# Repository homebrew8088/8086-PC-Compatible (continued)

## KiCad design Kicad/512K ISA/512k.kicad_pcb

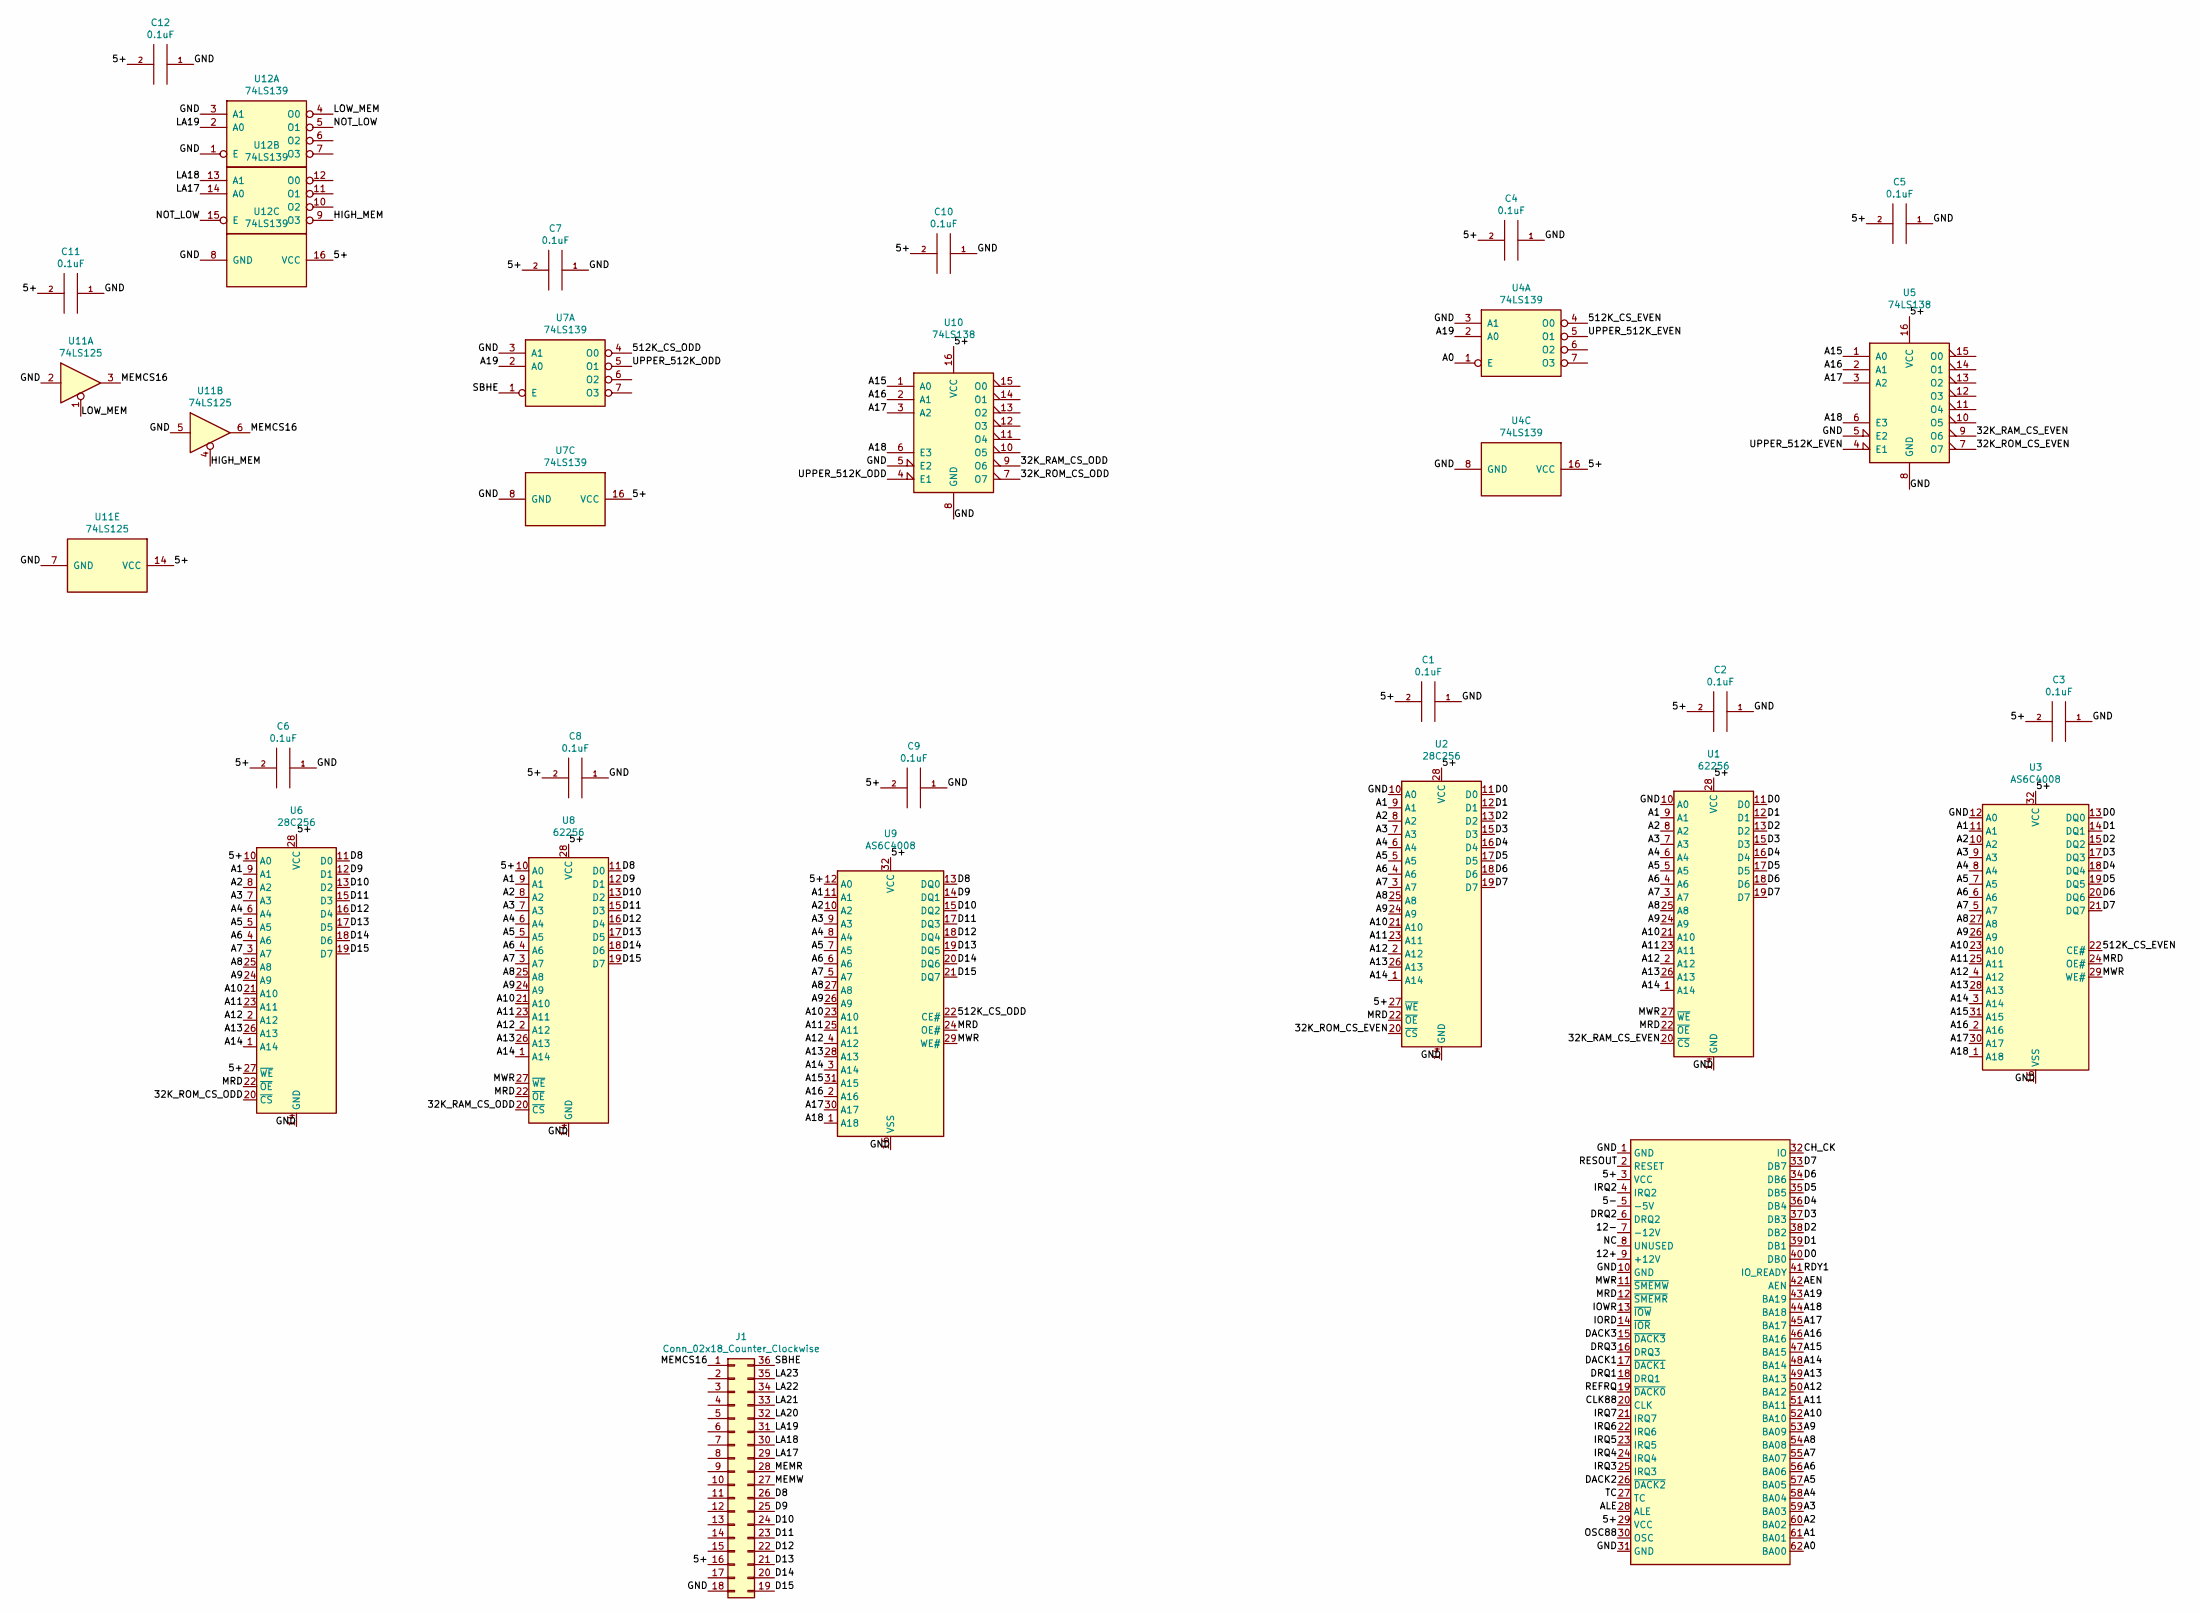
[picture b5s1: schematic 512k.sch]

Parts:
C1, C2, C3, C4, C5, C6, C7, C8, C9, C10, C11, C12: 0.1uF; C_Disc_D4.3mm_W1.9mm_P5.00mm
J1: Conn_02x18_Counter_Clockwise; 36_EDGE_CARD_BUS
J9: Bus_ISA_8bit; BUS_8_BIT
U1, U8: 62256; DIP-28_W15.24mm
U2, U6: 28C256; DIP_Socket-28_W11.9_W12.7_W15.24_W17.78_W18.5_3M_228-1277-0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
U3, U9: AS6C4008; DIP-32_W15.24mm
U4, U7, U12: 74LS139; DIP-16_W7.62mm
U5, U10: 74LS138; DIP-16_W7.62mm
U11: 74LS125; DIP-14_W7.62mm

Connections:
/5+: C1.2, C2.2, C3.2, C4.2, C5.2, C6.2, C7.2, C8.2, C9.2, C10.2, C11.2, C12.2, J1.16, J9.3 (VCC), J9.29 (VCC), U1.28 (VCC), U2.27 (~WE), U2.28 (VCC), U3.32 (VCC), U4.16 (VCC), U5.16 (VCC), U6.10 (A0), U6.27 (~WE), U6.28 (VCC), U7.16 (VCC), U8.10 (A0), U8.28 (VCC), U9.12 (A0), U9.32 (VCC), U10.16 (VCC), U11.14 (VCC), U12.16 (VCC)
/5-: J9.5 (-5V)
/12+: J9.9 (+12V)
/12-: J9.7 (-12V)
/32K_RAM_CS_EVEN: U1.20 (~CS), U5.9 (O6)
/32K_RAM_CS_ODD: U8.20 (~CS), U10.9 (O6)
/32K_ROM_CS_EVEN: U2.20 (~CS), U5.7 (O7)
/32K_ROM_CS_ODD: U6.20 (~CS), U10.7 (O7)
/512K_CS_EVEN: U3.22 (CE#), U4.4 (O0)
/512K_CS_ODD: U7.4 (O0), U9.22 (CE#)
/A0: J9.62 (BA00), U4.1 (E)
/A1: J9.61 (BA01), U1.9 (A1), U2.9 (A1), U3.11 (A1), U6.9 (A1), U8.9 (A1), U9.11 (A1)
/A2: J9.60 (BA02), U1.8 (A2), U2.8 (A2), U3.10 (A2), U6.8 (A2), U8.8 (A2), U9.10 (A2)
/A3: J9.59 (BA03), U1.7 (A3), U2.7 (A3), U3.9 (A3), U6.7 (A3), U8.7 (A3), U9.9 (A3)
/A4: J9.58 (BA04), U1.6 (A4), U2.6 (A4), U3.8 (A4), U6.6 (A4), U8.6 (A4), U9.8 (A4)
/A5: J9.57 (BA05), U1.5 (A5), U2.5 (A5), U3.7 (A5), U6.5 (A5), U8.5 (A5), U9.7 (A5)
/A6: J9.56 (BA06), U1.4 (A6), U2.4 (A6), U3.6 (A6), U6.4 (A6), U8.4 (A6), U9.6 (A6)
/A7: J9.55 (BA07), U1.3 (A7), U2.3 (A7), U3.5 (A7), U6.3 (A7), U8.3 (A7), U9.5 (A7)
/A8: J9.54 (BA08), U1.25 (A8), U2.25 (A8), U3.27 (A8), U6.25 (A8), U8.25 (A8), U9.27 (A8)
/A9: J9.53 (BA09), U1.24 (A9), U2.24 (A9), U3.26 (A9), U6.24 (A9), U8.24 (A9), U9.26 (A9)
/A10: J9.52 (BA10), U1.21 (A10), U2.21 (A10), U3.23 (A10), U6.21 (A10), U8.21 (A10), U9.23 (A10)
/A11: J9.51 (BA11), U1.23 (A11), U2.23 (A11), U3.25 (A11), U6.23 (A11), U8.23 (A11), U9.25 (A11)
/A12: J9.50 (BA12), U1.2 (A12), U2.2 (A12), U3.4 (A12), U6.2 (A12), U8.2 (A12), U9.4 (A12)
/A13: J9.49 (BA13), U1.26 (A13), U2.26 (A13), U3.28 (A13), U6.26 (A13), U8.26 (A13), U9.28 (A13)
/A14: J9.48 (BA14), U1.1 (A14), U2.1 (A14), U3.3 (A14), U6.1 (A14), U8.1 (A14), U9.3 (A14)
/A15: J9.47 (BA15), U3.31 (A15), U5.1 (A0), U9.31 (A15), U10.1 (A0)
/A16: J9.46 (BA16), U3.2 (A16), U5.2 (A1), U9.2 (A16), U10.2 (A1)
/A17: J9.45 (BA17), U3.30 (A17), U5.3 (A2), U9.30 (A17), U10.3 (A2)
/A18: J9.44 (BA18), U3.1 (A18), U5.6 (E3), U9.1 (A18), U10.6 (E3)
/A19: J9.43 (BA19), U4.2 (A0), U7.2 (A0)
/AEN: J9.42 (AEN)
/ALE: J9.28 (ALE)
/CH_CK: J9.32 (IO)
/CLK88: J9.20 (CLK)
/D0: J9.40 (DB0), U1.11 (D0), U2.11 (D0), U3.13 (DQ0)
/D1: J9.39 (DB1), U1.12 (D1), U2.12 (D1), U3.14 (DQ1)
/D2: J9.38 (DB2), U1.13 (D2), U2.13 (D2), U3.15 (DQ2)
/D3: J9.37 (DB3), U1.15 (D3), U2.15 (D3), U3.17 (DQ3)
/D4: J9.36 (DB4), U1.16 (D4), U2.16 (D4), U3.18 (DQ4)
/D5: J9.35 (DB5), U1.17 (D5), U2.17 (D5), U3.19 (DQ5)
/D6: J9.34 (DB6), U1.18 (D6), U2.18 (D6), U3.20 (DQ6)
/D7: J9.33 (DB7), U1.19 (D7), U2.19 (D7), U3.21 (DQ7)
/D8: J1.26, U6.11 (D0), U8.11 (D0), U9.13 (DQ0)
/D9: J1.25, U6.12 (D1), U8.12 (D1), U9.14 (DQ1)
/D10: J1.24, U6.13 (D2), U8.13 (D2), U9.15 (DQ2)
/D11: J1.23, U6.15 (D3), U8.15 (D3), U9.17 (DQ3)
/D12: J1.22, U6.16 (D4), U8.16 (D4), U9.18 (DQ4)
/D13: J1.21, U6.17 (D5), U8.17 (D5), U9.19 (DQ5)
/D14: J1.20, U6.18 (D6), U8.18 (D6), U9.20 (DQ6)
/D15: J1.19, U6.19 (D7), U8.19 (D7), U9.21 (DQ7)
/DACK1: J9.17 (~DACK1)
/DACK2: J9.26 (~DACK2)
/DACK3: J9.15 (~DACK3)
/DRQ1: J9.18 (DRQ1)
/DRQ2: J9.6 (DRQ2)
/DRQ3: J9.16 (DRQ3)
/GND: C1.1, C2.1, C3.1, C4.1, C5.1, C6.1, C7.1, C8.1, C9.1, C10.1, C11.1, C12.1, J1.18, J9.1 (GND), J9.10 (GND), J9.31 (GND), U1.10 (A0), U1.14 (GND), U2.10 (A0), U2.14 (GND), U3.12 (A0), U3.16 (VSS), U4.3 (A1), U4.8 (GND), U5.5 (E2), U5.8 (GND), U6.14 (GND), U7.3 (A1), U7.8 (GND), U8.14 (GND), U9.16 (VSS), U10.5 (E2), U10.8 (GND), U11.2, U11.5, U11.7 (GND), U12.1 (E), U12.3 (A1), U12.8 (GND); also elsewhere on the board
/HIGH_MEM: U11.4, U12.9 (O3)
/IORD: J9.14 (~IOR)
/IOWR: J9.13 (~IOW)
/IRQ2: J9.4 (IRQ2)
/IRQ3: J9.25 (IRQ3)
/IRQ4: J9.24 (IRQ4)
/IRQ5: J9.23 (IRQ5)
/IRQ6: J9.22 (IRQ6)
/IRQ7: J9.21 (IRQ7)
/LA17: J1.29, U12.14 (A0)
/LA18: J1.30, U12.13 (A1)
/LA19: J1.31, U12.2 (A0)
/LA20: J1.32
/LA21: J1.33
/LA22: J1.34
/LA23: J1.35
/LOW_MEM: U11.1, U12.4 (O0)
/MEMCS16: J1.1, U11.3, U11.6
/MEMR: J1.28
/MEMW: J1.27
/MRD: J9.12 (~SMEMR), U1.22 (~OE), U2.22 (~OE), U3.24 (OE#), U6.22 (~OE), U8.22 (~OE), U9.24 (OE#)
/MWR: J9.11 (~SMEMW), U1.27 (~WE), U3.29 (WE#), U8.27 (~WE), U9.29 (WE#)
/NC: J9.8 (UNUSED)
/NOT_LOW: U12.5 (O1), U12.15 (E)
/OSC88: J9.30 (OSC)
/RDY1: J9.41 (IO_READY)
/REFRQ: J9.19 (~DACK0)
/RESOUT: J9.2 (RESET)
/SBHE: J1.36, U7.1 (E)
/TC: J9.27 (TC)
/UPPER_512K_EVEN: U4.5 (O1), U5.4 (E1)
/UPPER_512K_ODD: U7.5 (O1), U10.4 (E1)

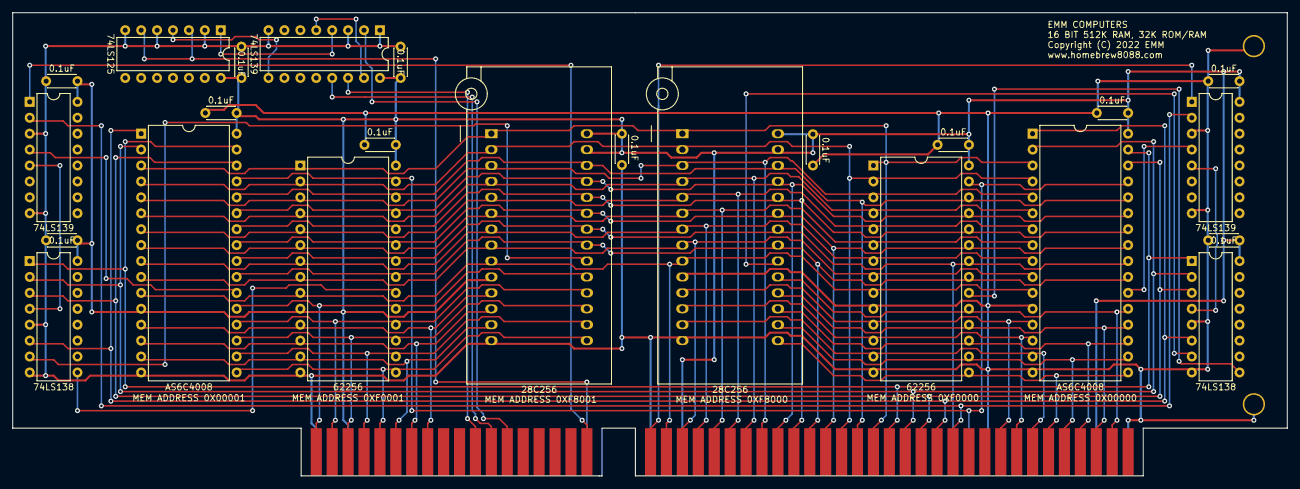
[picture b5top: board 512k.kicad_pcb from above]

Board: 2 copper layers, 203.4 x 73.9 mm, 28 parts (0 on the bottom side), 56 nets.

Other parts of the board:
R: L; Large_Via
R#2: L; Large_Via

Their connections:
/GND: R.1, R#2.1; also elsewhere on the board

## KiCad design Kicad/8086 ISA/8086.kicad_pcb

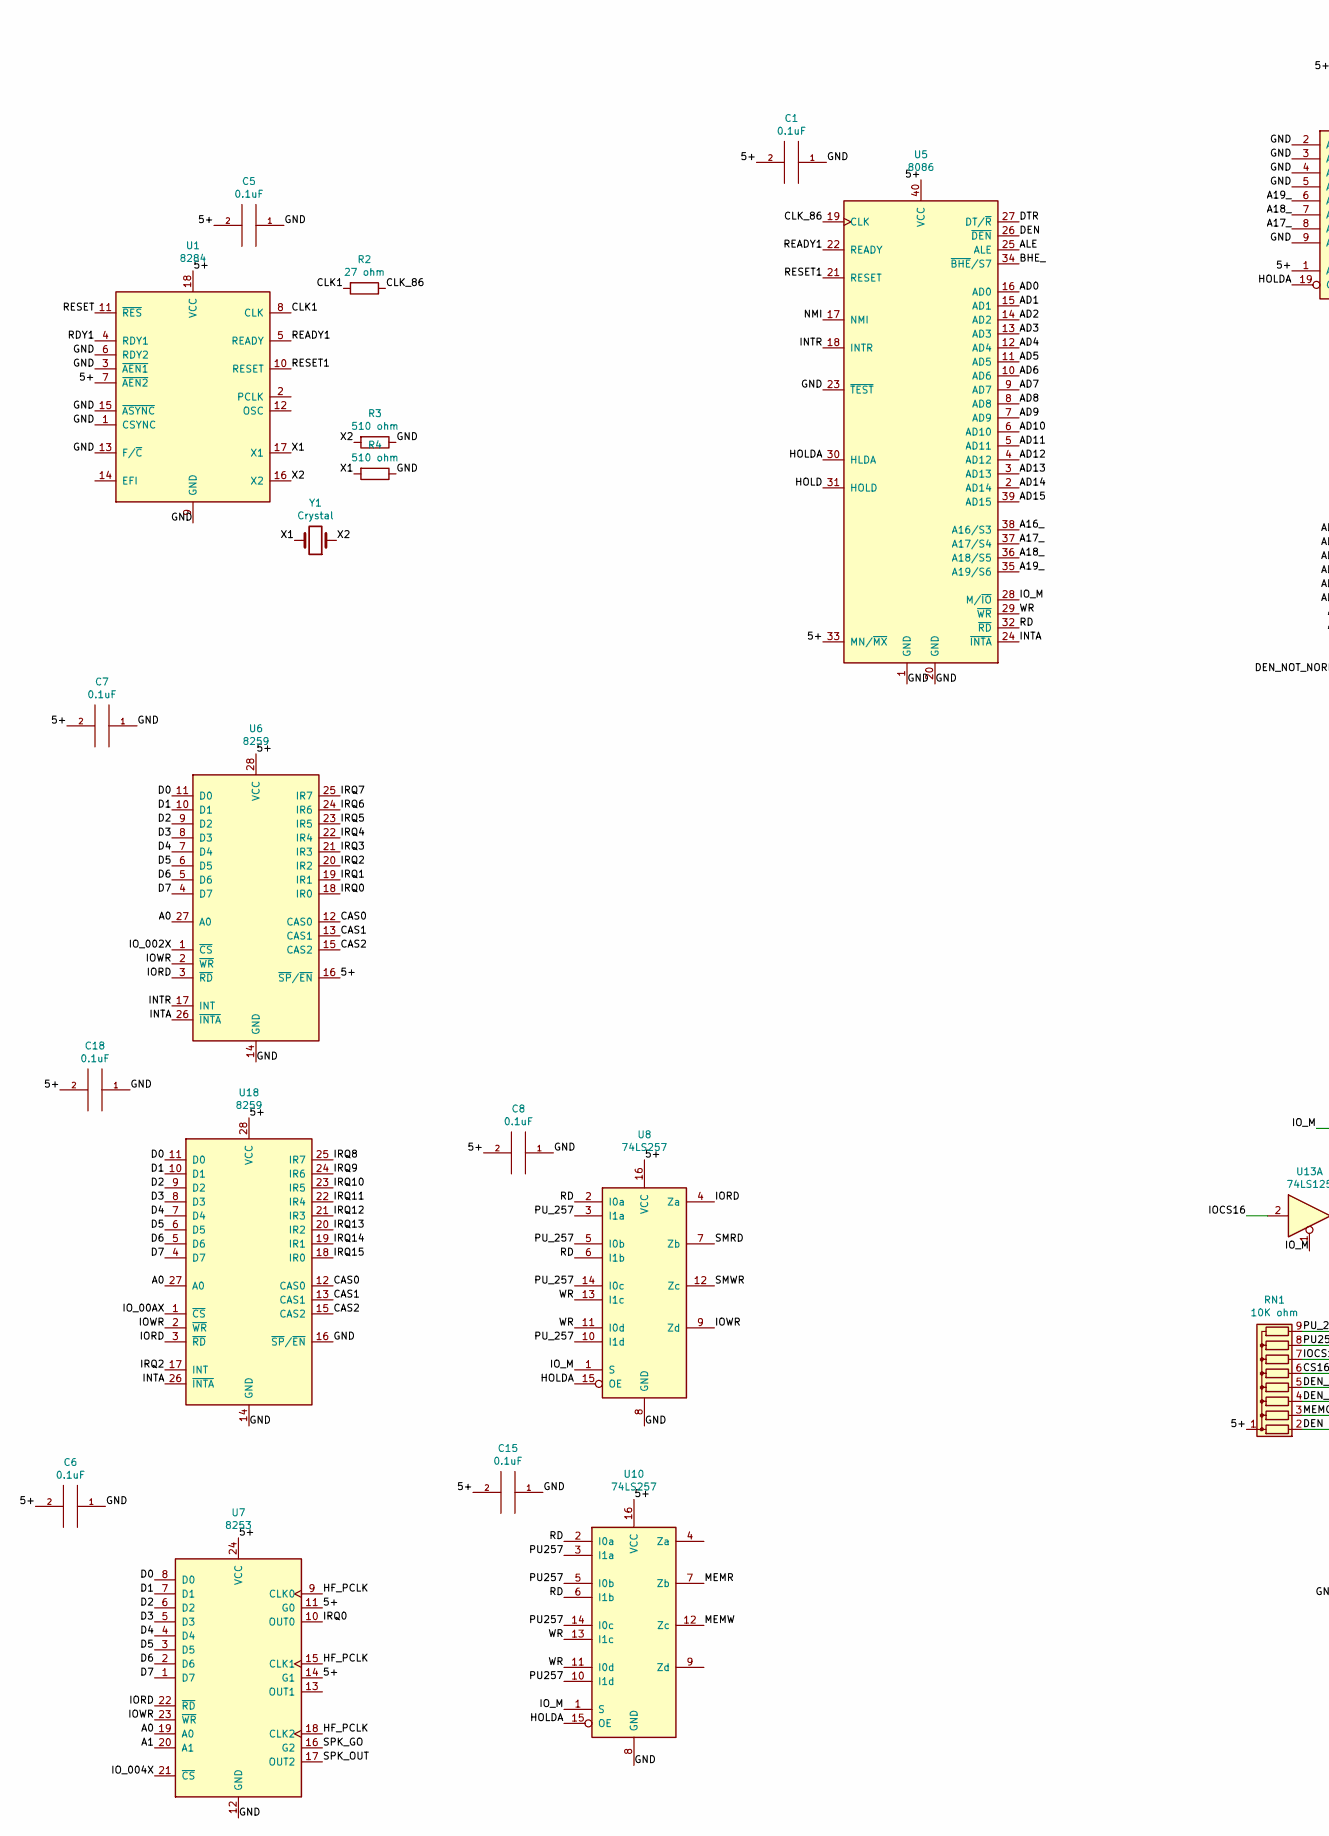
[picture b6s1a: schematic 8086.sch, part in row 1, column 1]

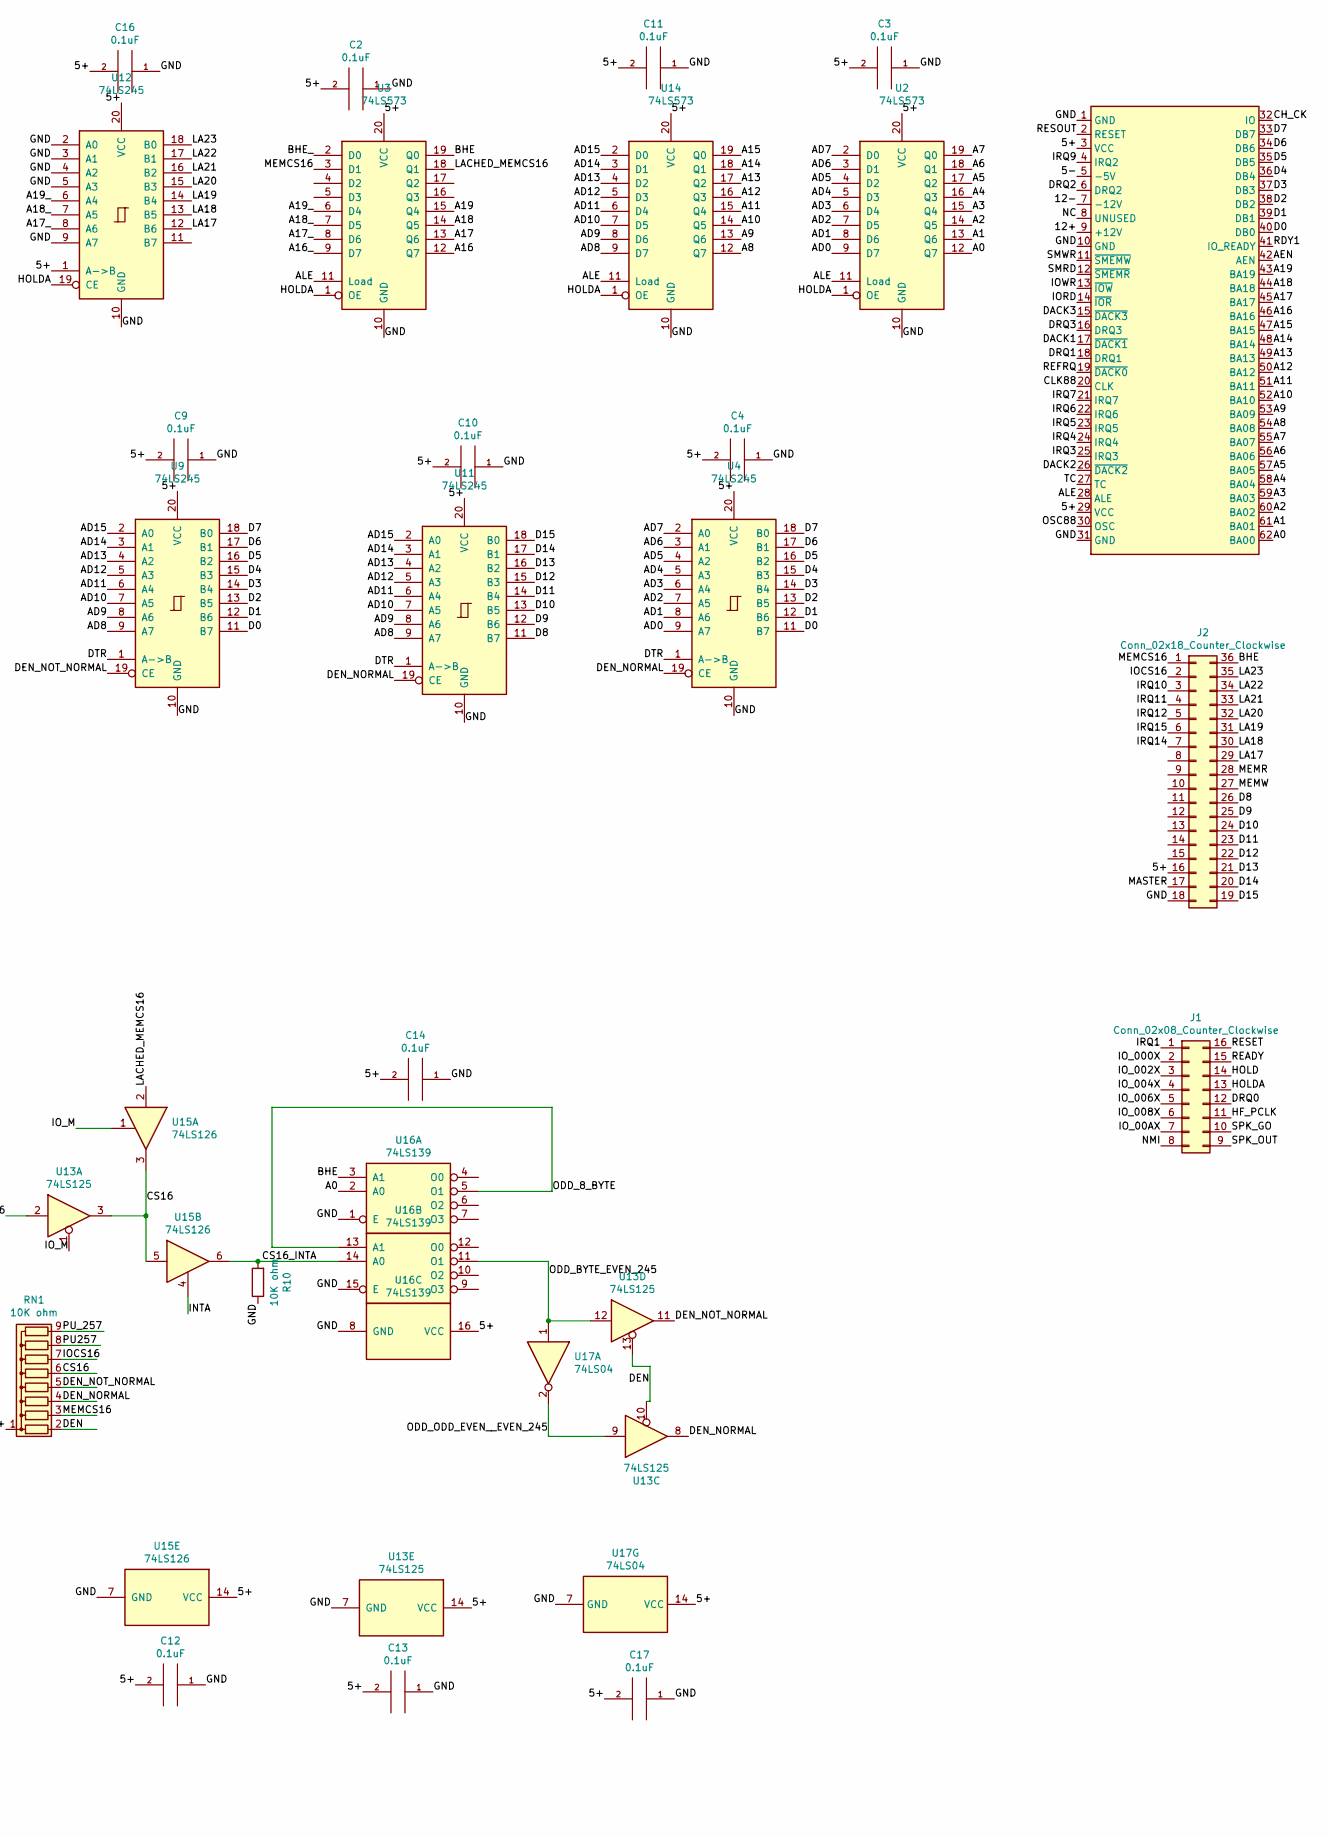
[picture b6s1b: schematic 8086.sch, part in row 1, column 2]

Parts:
C1, C2, C3, C4, C5, C6, C7, C8, C9, C10, C11, C12, C13, C14, C15, C16, C17, C18: 0.1uF; C_Disc_D4.3mm_W1.9mm_P5.00mm
J1: Conn_02x08_Counter_Clockwise; 16_EDGE_CARD_BUS
J2: Conn_02x18_Counter_Clockwise; 36_EDGE_CARD_BUS
J9: Bus_ISA_8bit; BUS_8_BIT
R2: 27 ohm; R_Axial_DIN0207_L6.3mm_D2.5mm_P10.16mm_Horizontal
R3, R4: 510 ohm; R_Axial_DIN0207_L6.3mm_D2.5mm_P10.16mm_Horizontal
R10: 10K ohm; R_Axial_DIN0207_L6.3mm_D2.5mm_P10.16mm_Horizontal
RN1: 10K ohm; R_Array_SIP9
U1: 8284; DIP-18_W7.62mm
U2, U3, U14: 74LS573; DIP-20_W7.62mm
U4, U9, U11, U12: 74LS245; DIP-20_W7.62mm
U5: 8086; DIP-40_W15.24mm
U6, U18: 8259; DIP-28_W15.24mm
U7: 8253; DIP-24_W15.24mm
U8, U10: 74LS257; DIP-16_W7.62mm
U13: 74LS125; DIP-14_W7.62mm
U15: 74LS126; DIP-14_W7.62mm
U16: 74LS139; DIP-16_W7.62mm
U17: 74LS04; DIP-14_W7.62mm
Y1: Crystal; Crystal_HC18-U_Vertical

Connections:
/5+: C1.2, C2.2, C3.2, C4.2, C5.2, C6.2, C7.2, C8.2, C9.2, C10.2, C11.2, C12.2, C13.2, C14.2, C15.2, C16.2, C17.2, C18.2, J2.16, J9.3 (VCC), J9.29 (VCC), RN1.1 (common), U1.7 (~AEN2~), U1.18 (VCC), U2.20 (VCC), U3.20 (VCC), U4.20 (VCC), U5.33 (MN/~MX~), U5.40 (VCC), U6.16 (~SP~/~EN~), U6.28 (VCC), U7.11 (G0), U7.14 (G1), U7.24 (VCC), U8.16 (VCC), U9.20 (VCC), U10.16 (VCC), U11.20 (VCC), U12.1 (A->B), U12.20 (VCC), U13.14 (VCC), U14.20 (VCC), U15.14 (VCC), U16.16 (VCC), U17.14 (VCC), U18.28 (VCC)
/5-: J9.5 (-5V)
/12+: J9.9 (+12V)
/12-: J9.7 (-12V)
/A0: J9.62 (BA00), U2.12 (Q7), U6.27 (A0), U7.19 (A0), U16.2 (A0), U18.27 (A0)
/A1: J9.61 (BA01), U2.13 (Q6), U7.20 (A1)
/A2: J9.60 (BA02), U2.14 (Q5)
/A3: J9.59 (BA03), U2.15 (Q4)
/A4: J9.58 (BA04), U2.16 (Q3)
/A5: J9.57 (BA05), U2.17 (Q2)
/A6: J9.56 (BA06), U2.18 (Q1)
/A7: J9.55 (BA07), U2.19 (Q0)
/A8: J9.54 (BA08), U14.12 (Q7)
/A9: J9.53 (BA09), U14.13 (Q6)
/A10: J9.52 (BA10), U14.14 (Q5)
/A11: J9.51 (BA11), U14.15 (Q4)
/A12: J9.50 (BA12), U14.16 (Q3)
/A13: J9.49 (BA13), U14.17 (Q2)
/A14: J9.48 (BA14), U14.18 (Q1)
/A15: J9.47 (BA15), U14.19 (Q0)
/A16: J9.46 (BA16), U3.12 (Q7)
/A16_: U3.9 (D7), U5.38 (A16/S3)
/A17: J9.45 (BA17), U3.13 (Q6)
/A17_: U3.8 (D6), U5.37 (A17/S4), U12.8 (A6)
/A18: J9.44 (BA18), U3.14 (Q5)
/A18_: U3.7 (D5), U5.36 (A18/S5), U12.7 (A5)
/A19: J9.43 (BA19), U3.15 (Q4)
/A19_: U3.6 (D4), U5.35 (A19/S6), U12.6 (A4)
/AD0: U2.9 (D7), U4.9 (A7), U5.16 (AD0)
/AD1: U2.8 (D6), U4.8 (A6), U5.15 (AD1)
/AD2: U2.7 (D5), U4.7 (A5), U5.14 (AD2)
/AD3: U2.6 (D4), U4.6 (A4), U5.13 (AD3)
/AD4: U2.5 (D3), U4.5 (A3), U5.12 (AD4)
/AD5: U2.4 (D2), U4.4 (A2), U5.11 (AD5)
/AD6: U2.3 (D1), U4.3 (A1), U5.10 (AD6)
/AD7: U2.2 (D0), U4.2 (A0), U5.9 (AD7)
/AD8: U5.8 (AD8), U9.9 (A7), U11.9 (A7), U14.9 (D7)
/AD9: U5.7 (AD9), U9.8 (A6), U11.8 (A6), U14.8 (D6)
/AD10: U5.6 (AD10), U9.7 (A5), U11.7 (A5), U14.7 (D5)
/AD11: U5.5 (AD11), U9.6 (A4), U11.6 (A4), U14.6 (D4)
/AD12: U5.4 (AD12), U9.5 (A3), U11.5 (A3), U14.5 (D3)
/AD13: U5.3 (AD13), U9.4 (A2), U11.4 (A2), U14.4 (D2)
/AD14: U5.2 (AD14), U9.3 (A1), U11.3 (A1), U14.3 (D1)
/AD15: U5.39 (AD15), U9.2 (A0), U11.2 (A0), U14.2 (D0)
/AEN: J9.42 (AEN)
/ALE: J9.28 (ALE), U2.11 (Load), U3.11 (Load), U5.25 (ALE), U14.11 (Load)
/BHE: J2.36, U3.19 (Q0), U16.3 (A1)
/BHE_: U3.2 (D0), U5.34 (~BHE~/S7)
/CAS0: U6.12 (CAS0), U18.12 (CAS0)
/CAS1: U6.13 (CAS1), U18.13 (CAS1)
/CAS2: U6.15 (CAS2), U18.15 (CAS2)
/CH_CK: J9.32 (IO)
/CLK1: R2.2, U1.8 (CLK)
/CLK88: J9.20 (CLK)
/CLK_86: R2.1, U5.19 (CLK)
/CS16: RN1.6 (R5), U13.3, U15.3, U15.5
/CS16_INTA: R10.2, U15.6, U16.14 (A0)
/D0: J9.40 (DB0), U4.11 (B7), U6.11 (D0), U7.8 (D0), U9.11 (B7), U18.11 (D0)
/D1: J9.39 (DB1), U4.12 (B6), U6.10 (D1), U7.7 (D1), U9.12 (B6), U18.10 (D1)
/D2: J9.38 (DB2), U4.13 (B5), U6.9 (D2), U7.6 (D2), U9.13 (B5), U18.9 (D2)
/D3: J9.37 (DB3), U4.14 (B4), U6.8 (D3), U7.5 (D3), U9.14 (B4), U18.8 (D3)
/D4: J9.36 (DB4), U4.15 (B3), U6.7 (D4), U7.4 (D4), U9.15 (B3), U18.7 (D4)
/D5: J9.35 (DB5), U4.16 (B2), U6.6 (D5), U7.3 (D5), U9.16 (B2), U18.6 (D5)
/D6: J9.34 (DB6), U4.17 (B1), U6.5 (D6), U7.2 (D6), U9.17 (B1), U18.5 (D6)
/D7: J9.33 (DB7), U4.18 (B0), U6.4 (D7), U7.1 (D7), U9.18 (B0), U18.4 (D7)
/D8: J2.26, U11.11 (B7)
/D9: J2.25, U11.12 (B6)
/D10: J2.24, U11.13 (B5)
/D11: J2.23, U11.14 (B4)
/D12: J2.22, U11.15 (B3)
/D13: J2.21, U11.16 (B2)
/D14: J2.20, U11.17 (B1)
/D15: J2.19, U11.18 (B0)
/DACK1: J9.17 (~DACK1)
/DACK2: J9.26 (~DACK2)
/DACK3: J9.15 (~DACK3)
/DEN: RN1.2 (R1), U5.26 (~DEN~), U13.10, U13.13
/DEN_NORMAL: RN1.4 (R3), U4.19 (CE), U11.19 (CE), U13.8
/DEN_NOT_NORMAL: RN1.5 (R4), U9.19 (CE), U13.11
/DRQ0: J1.12
/DRQ1: J9.18 (DRQ1)
/DRQ2: J9.6 (DRQ2)
/DRQ3: J9.16 (DRQ3)
/DTR: U4.1 (A->B), U5.27 (DT/~R~), U9.1 (A->B), U11.1 (A->B)
/GND: C1.1, C2.1, C3.1, C4.1, C5.1, C6.1, C7.1, C8.1, C9.1, C10.1, C11.1, C12.1, C13.1, C14.1, C15.1, C16.1, C17.1, C18.1, J2.18, J9.1 (GND), J9.10 (GND), J9.31 (GND), R3.1, R4.1, R10.1, U1.1 (CSYNC), U1.3 (~AEN1~), U1.6 (RDY2), U1.9 (GND), U1.13 (F/~C~), U1.15 (~ASYNC~), U2.10 (GND), U3.10 (GND), U4.10 (GND), U5.1 (GND), U5.20 (GND), U5.23 (~TEST~), U6.14 (GND), U7.12 (GND), U8.8 (GND), U9.10 (GND), U10.8 (GND), U11.10 (GND), U12.2 (A0), U12.3 (A1), U12.4 (A2), U12.5 (A3), U12.9 (A7), U12.10 (GND), U13.7 (GND), U14.10 (GND), U15.7 (GND), U16.1 (E), U16.8 (GND), U16.15 (E), U17.7 (GND), U18.14 (GND), U18.16 (~SP~/~EN~); also elsewhere on the board
/HF_PCLK: J1.11, U7.9 (CLK0), U7.15 (CLK1), U7.18 (CLK2)
/HOLD: J1.14, U5.31 (HOLD)
/HOLDA: J1.13, U2.1 (OE), U3.1 (OE), U5.30 (HLDA), U8.15 (OE), U10.15 (OE), U12.19 (CE), U14.1 (OE)
/INTA: U5.24 (~INTA~), U6.26 (~INTA~), U15.4, U18.26 (~INTA~)
/INTR: U5.18 (INTR), U6.17 (INT)
/IOCS16: J2.2, RN1.7 (R6), U13.2
/IORD: J9.14 (~IOR), U6.3 (~RD~), U7.22 (~RD~), U8.4 (Za), U18.3 (~RD~)
/IOWR: J9.13 (~IOW), U6.2 (~WR~), U7.23 (~WR~), U8.9 (Zd), U18.2 (~WR~)
/IO_00AX: J1.7, U18.1 (~CS~)
/IO_000X: J1.2
/IO_002X: J1.3, U6.1 (~CS~)
/IO_004X: J1.4, U7.21 (~CS~)
/IO_006X: J1.5
/IO_008X: J1.6
/IO_M: U5.28 (M/~IO~), U8.1 (S), U10.1 (S), U13.1, U15.1
/IRQ0: U6.18 (IR0), U7.10 (OUT0)
/IRQ1: J1.1, U6.19 (IR1)
/IRQ2: U6.20 (IR2), U18.17 (INT)
/IRQ3: J9.25 (IRQ3), U6.21 (IR3)
/IRQ4: J9.24 (IRQ4), U6.22 (IR4)
/IRQ5: J9.23 (IRQ5), U6.23 (IR5)
/IRQ6: J9.22 (IRQ6), U6.24 (IR6)
/IRQ7: J9.21 (IRQ7), U6.25 (IR7)
/IRQ8: U18.25 (IR7)
/IRQ9: J9.4 (IRQ2), U18.24 (IR6)
/IRQ10: J2.3, U18.23 (IR5)
/IRQ11: J2.4, U18.22 (IR4)
/IRQ12: J2.5, U18.21 (IR3)
/IRQ13: U18.20 (IR2)
/IRQ14: J2.7, U18.19 (IR1)
/IRQ15: J2.6, U18.18 (IR0)
/LA17: J2.29, U12.12 (B6)
/LA18: J2.30, U12.13 (B5)
/LA19: J2.31, U12.14 (B4)
/LA20: J2.32, U12.15 (B3)
/LA21: J2.33, U12.16 (B2)
/LA22: J2.34, U12.17 (B1)
/LA23: J2.35, U12.18 (B0)
/LACHED_MEMCS16: U3.18 (Q1), U15.2
/MASTER: J2.17
/MEMCS16: J2.1, RN1.3 (R2), U3.3 (D1)
/MEMR: J2.28, U10.7 (Zb)
/MEMW: J2.27, U10.12 (Zc)
/NC: J9.8 (UNUSED)
/NMI: J1.8, U5.17 (NMI)
/ODD_8_BYTE: U16.5 (O1), U16.13 (A1)
/ODD_BYTE_EVEN_245: U13.12, U16.11 (O1), U17.1
/ODD_ODD_EVEN__EVEN_245: U13.9, U17.2
/OSC88: J9.30 (OSC)
/PU257: RN1.8 (R7), U10.3 (I1a), U10.5 (I0b), U10.10 (I1d), U10.14 (I0c)
/PU_257: RN1.9 (R8), U8.3 (I1a), U8.5 (I0b), U8.10 (I1d), U8.14 (I0c)
/RD: U5.32 (~RD~), U8.2 (I0a), U8.6 (I1b), U10.2 (I0a), U10.6 (I1b)
/RDY1: J9.41 (IO_READY), U1.4 (RDY1)
/READY: J1.15
/READY1: U1.5 (READY), U5.22 (READY)
/REFRQ: J9.19 (~DACK0)
/RESET: J1.16, U1.11 (~RES~)
/RESET1: U1.10 (RESET), U5.21 (RESET)
/RESOUT: J9.2 (RESET)
/SMRD: J9.12 (~SMEMR), U8.7 (Zb)
/SMWR: J9.11 (~SMEMW), U8.12 (Zc)
/SPK_GO: J1.10, U7.16 (G2)
/SPK_OUT: J1.9, U7.17 (OUT2)
/TC: J9.27 (TC)
/WR: U5.29 (~WR~), U8.11 (I0d), U8.13 (I1c), U10.11 (I0d), U10.13 (I1c)
/X1: R4.2, U1.17 (X1), Y1.2
/X2: R3.2, U1.16 (X2), Y1.1

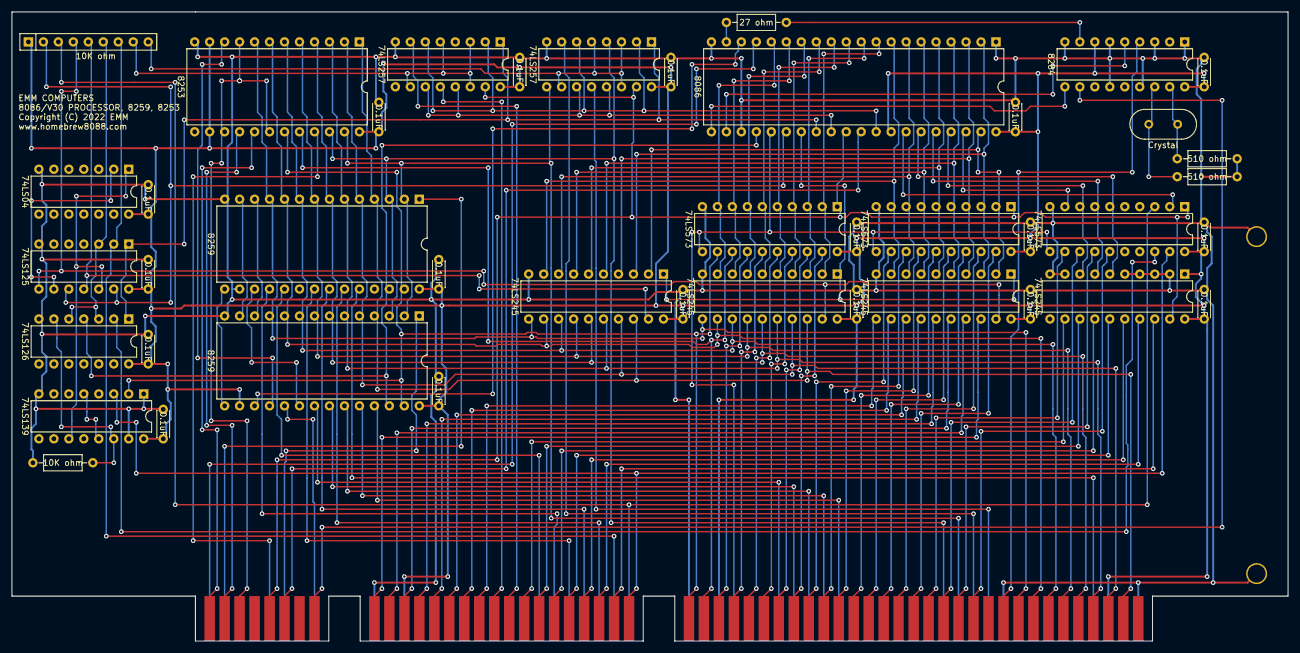
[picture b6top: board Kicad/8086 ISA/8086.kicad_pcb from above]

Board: 2 copper layers, 216.4 x 106.7 mm, 47 parts (0 on the bottom side), 127 nets.

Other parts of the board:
R: L; Large_Via
R#2: L; Large_Via

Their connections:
/GND: R.1, R#2.1; also elsewhere on the board

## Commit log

2021-12-06 initial upload
2021-12-06 Rename
2022-01-04 Added Kicad files
2022-04-16 added LCD BIOS
2022-07-20 minor change
2022-07-20 Added some kicad
2025-05-06 updating 8086 card
2025-05-06 updated BUS micro code
